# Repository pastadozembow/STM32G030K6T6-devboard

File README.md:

This board was designed to be as cheap as possible while remaining fast and flexible to use. It can be powered by a 12v source via the vin pin, It has a 64mhz 32bit ARM MCU and can be flashed via an USB port which is connected to an USB to UART converter.
5 boards assembled by hand cost 20$(converted from PLN so it can be cheaper depending on your component source and country)
If you have any issues or ideas for improvments DM me on discord: lorbasta

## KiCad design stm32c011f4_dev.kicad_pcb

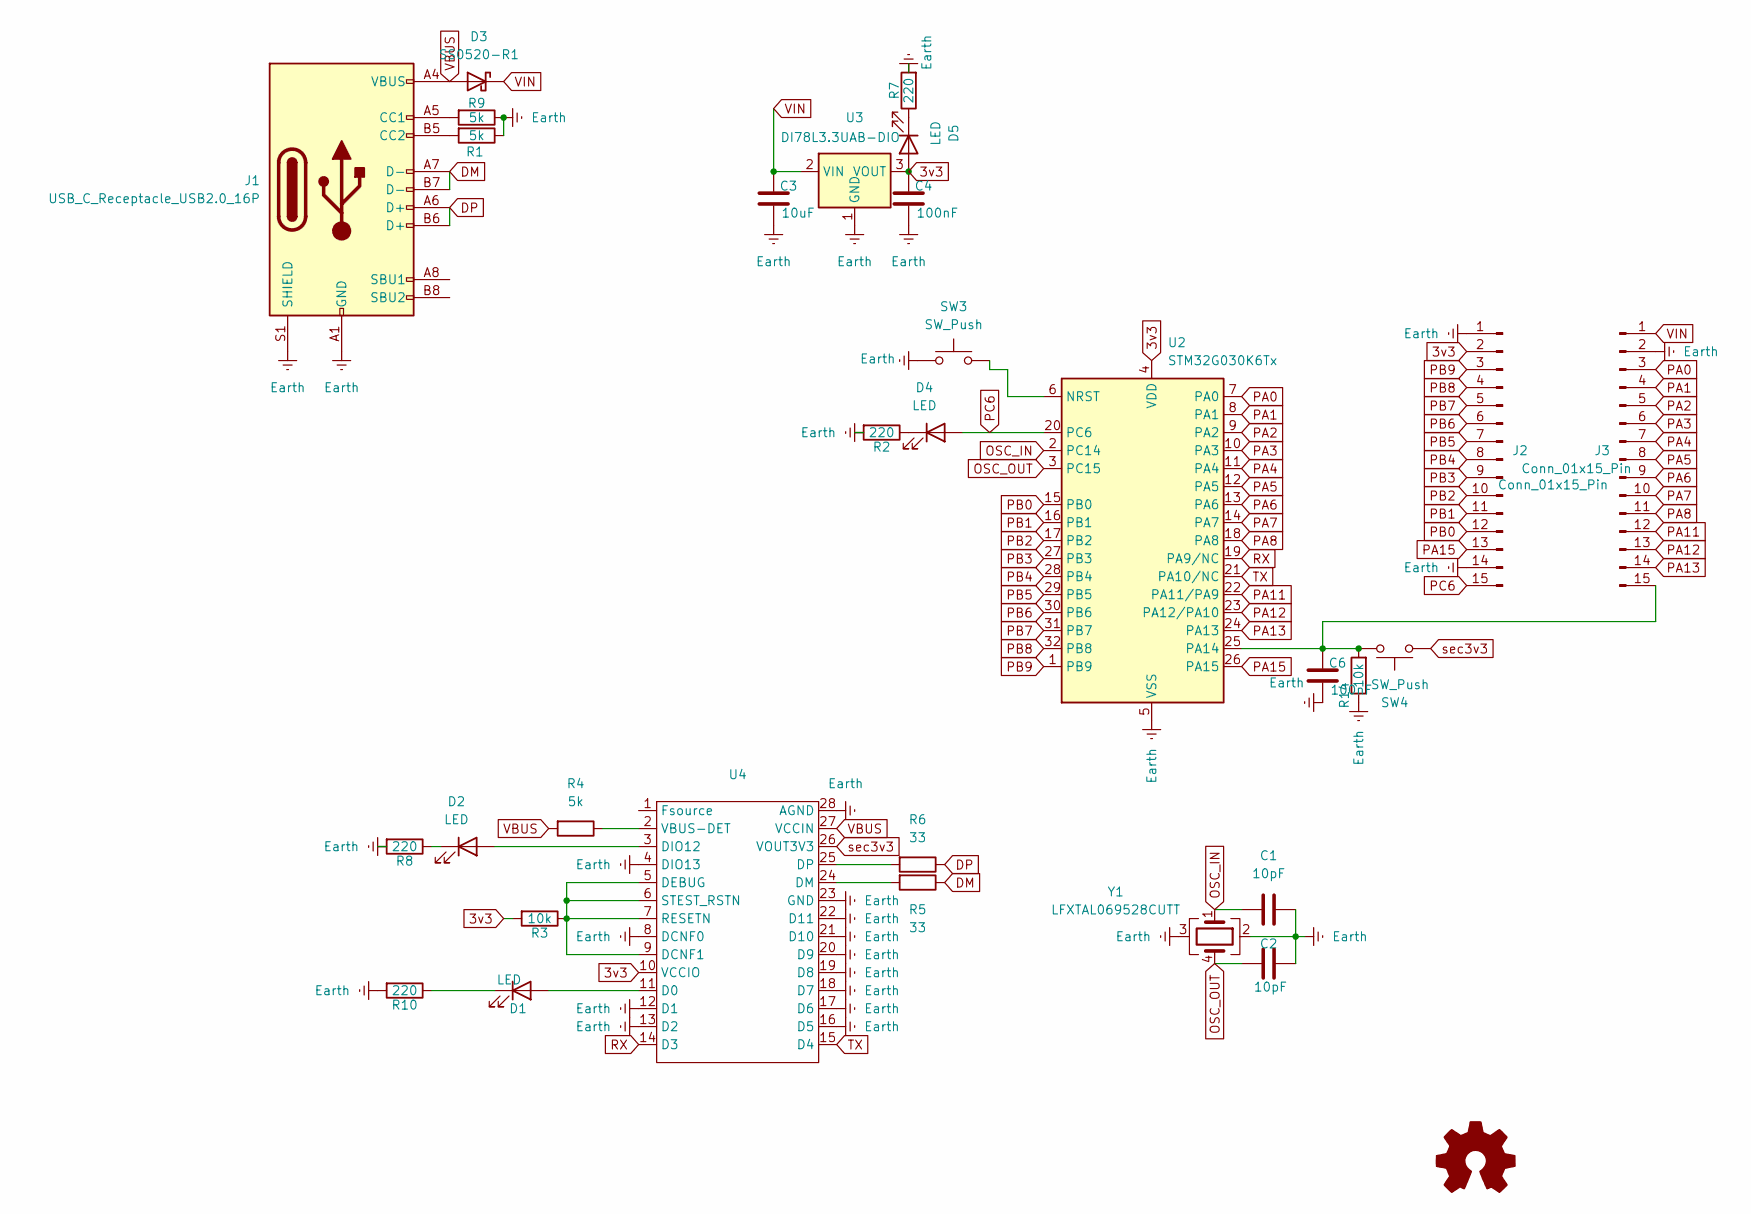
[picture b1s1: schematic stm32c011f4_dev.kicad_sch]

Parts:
C1, C2: 10pF; C_0603_1608Metric
C3: 10uF; C_1206_3216Metric
C4, C6: 100nF; C_0603_1608Metric
D1, D2, D4, D5: LED; LED_0603_1608Metric
D3: SS0520-R1; D_SOD-123
J1: USB_C_Receptacle_USB2.0_16P; USB_C_Receptacle_GCT_USB4085
J2, J3: Conn_01x15_Pin; PinHeader_1x15_P2.54mm_Vertical
R1, R4, R9: 5k; R_0603_1608Metric
R2, R7, R8, R10: 220; R_0603_1608Metric
R3, R14: 10k; R_0603_1608Metric
R5, R6: 33; R_0603_1608Metric
SW3, SW4: SW_Push; SW_SPST_EVQQ2
U2: STM32G030K6Tx; LQFP-32_7x7mm_P0.8mm
U3: DI78L3.3UAB-DIO; SOT-89-3
U4: FT260S-U
Y1: LFXTAL069528CUTT; Crystal_SMD_2016-4Pin_2.0x1.6mm

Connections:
3v3: C4.1, D5.2 (A), J2.2, R3.2, U2.4 (VDD), U3.3 (VOUT), U4.10 (VCCIO)
DM: J1.A7 (D-), J1.B7 (D-), R5.1
DP: J1.A6 (D+), J1.B6 (D+), R6.1
Earth: C1.2, C2.2, C3.2, C4.2, C6.2, J1.A1 (GND), J1.A12 (GND), J1.B1 (GND), J1.B12 (GND), J1.S1 (SHIELD), J2.1, J2.14, J3.2, R1.1, R2.2, R7.2, R8.2, R9.1, R10.2, R14.1, SW3.1, U2.5 (VSS), U3.1 (GND), U4.4 (DIO13), U4.8 (DCNF0), U4.12 (D1), U4.13 (D2), U4.16 (D5), U4.17 (D6), U4.18 (D7), U4.19 (D8), U4.20 (D9), U4.21 (D10), U4.22 (D11), U4.23 (GND), U4.28 (AGND), Y1.2, Y1.3
unnamed: D1.2 (A), U4.11 (D0)
unnamed: D1.1 (K), R10.1
unnamed: D2.2 (A), U4.3 (DIO12)
unnamed: D2.1 (K), R8.1
unnamed: D4.1 (K), R2.1
unnamed: D5.1 (K), R7.1
unnamed: J1.A5 (CC1), R9.2
unnamed: J1.B5 (CC2), R1.2
unnamed: C6.1, J3.15, R14.2, SW4.1, U2.25 (PA14)
unnamed: SW3.2, U2.6 (NRST)
unnamed: R3.1, U4.5 (DEBUG), U4.6 (STEST_RSTN), U4.7 (RESETN), U4.9 (DCNF1)
unnamed: R5.2, U4.24 (DM)
unnamed: R6.2, U4.25 (DP)
unnamed: R4.1, U4.2 (VBUS-DET)
OSC_IN: C1.1, U2.2 (PC14), Y1.1
OSC_OUT: C2.1, U2.3 (PC15), Y1.4
PA0: J3.3, U2.7 (PA0)
PA1: J3.4, U2.8 (PA1)
PA2: J3.5, U2.9 (PA2)
PA3: J3.6, U2.10 (PA3)
PA4: J3.7, U2.11 (PA4)
PA5: J3.8, U2.12 (PA5)
PA6: J3.9, U2.13 (PA6)
PA7: J3.10, U2.14 (PA7)
PA8: J3.11, U2.18 (PA8)
PA11: J3.12, U2.22 (PA11/PA9)
PA12: J3.13, U2.23 (PA12/PA10)
PA13: J3.14, U2.24 (PA13)
PA15: J2.13, U2.26 (PA15)
PB0: J2.12, U2.15 (PB0)
PB1: J2.11, U2.16 (PB1)
PB2: J2.10, U2.17 (PB2)
PB3: J2.9, U2.27 (PB3)
PB4: J2.8, U2.28 (PB4)
PB5: J2.7, U2.29 (PB5)
PB6: J2.6, U2.30 (PB6)
PB7: J2.5, U2.31 (PB7)
PB8: J2.4, U2.32 (PB8)
PB9: J2.3, U2.1 (PB9)
PC6: D4.2 (A), J2.15, U2.20 (PC6)
RX: U2.19 (PA9/NC), U4.14 (D3)
TX: U2.21 (PA10/NC), U4.15 (D4)
VBUS: D3.2 (A), J1.A4 (VBUS), J1.A9 (VBUS), J1.B4 (VBUS), J1.B9 (VBUS), R4.2, U4.27 (VCCIN)
VIN: C3.1, D3.1 (K), J3.1, U3.2 (VIN)
sec3v3: SW4.2, U4.26 (VOUT3V3)

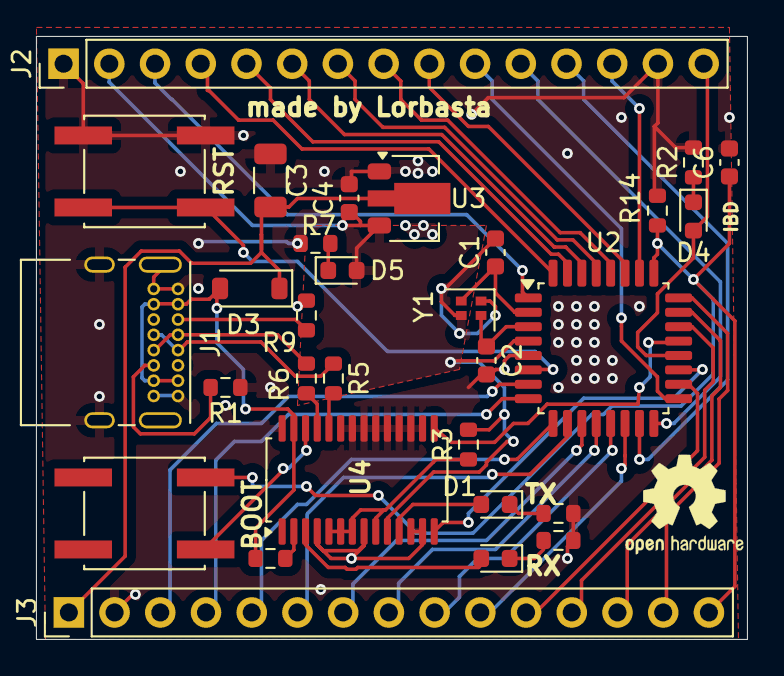
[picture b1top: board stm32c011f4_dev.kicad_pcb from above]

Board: 2 copper layers, 39.5 x 33.5 mm, 30 parts (0 on the bottom side), 49 nets.

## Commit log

2024-04-03 PCB and schematic on KiCAD
2024-04-03 KiCAD project
2024-04-03 Gerber file
2024-04-03 Gerber and pcb update
2024-04-03 pcb update
2024-04-04 Silkscreen update
2024-04-05 Create LICENSE
2024-04-05 pcb update
    fixed gnd mistakes
2024-04-09 PCB update
    adding swd and improving traces
2024-05-28 Changing usb-c from smt to tht
2024-06-19 tht usb and one resistor per led cathode
    :333
2024-06-19 tht usb and one resistor per cathode
    :33333
